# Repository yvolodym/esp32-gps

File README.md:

# esp32-gps

Akku-betriebenes GNSS-Empfänger-Board auf Basis des **ESP32**. Ein GNSS-Modul (GPS/BDS/GLONASS)
liefert die Positionsdaten, der ESP32 liest sie über UART aus und stellt sie per **Bluetooth**
für andere Geräte (z. B. Smartphone, Laptop, Navigationssoftware) bereit.

> Aktueller Stand: vollständiges KiCad-Hardwaredesign (Schaltplan + Platinenlayout). Die
> ESP32-Firmware (ESP-IDF) liest das GNSS-Modul per UART aus und gibt die NMEA-Sätze aktuell
> im Log aus; die Weiterleitung per Bluetooth folgt als nächster Schritt.

## Features

- **ESP32-PICO-V3** als zentrale MCU (WLAN + Bluetooth Classic/BLE integriert)
- **Ai-Thinker GP-01** GNSS-Modul (GPS/BDS/GLONASS) mit externer Antenne (Koax-Anschluss)
- **USB-C** für Programmierung (über integrierten CH340C USB-UART-Wandler) und zum Laden
- **Li-Ion-Akkubetrieb** (18650) mit Lade-IC TP4056, Akkuschutz (DW01A) und automatischer
  Umschaltung zwischen USB- und Akkuversorgung (LTC4412 Ideal-Diode-Power-Path)
- 3,3-V-Logikversorgung über AP2112K-3.3-LDO, ESD-Schutz am USB-Eingang

## Hardware

| Schaltplan | Inhalt |
|---|---|
| `kicad/esp32-gps.kicad_sch` | ESP32-PICO-V3, GNSS-Modul GP-01, USB-UART (CH340C), Antennenanschluss |
| `kicad/supply.kicad_sch` | Akku, Ladeschaltung, Power-Path, 3,3-V-Regler |
| `kicad/esp32-gps.kicad_pcb` | Platinenlayout |

Erstellt mit KiCad 9. Verwendete Zusatzbibliothek: [`yvolodym/kicad-libraries`](https://github.com/yvolodym).

## Firmware

ESP-IDF-Projekt (Framework-Version 6.0.2), Ziel-Chip `esp32`. Initialisiert UART2 auf den
Pins, die im Schaltplan als `GPS_TX`/`GPS_RX` verdrahtet sind (IO25/IO26), liest die NMEA-Sätze
des GP-01 zeilenweise ein und gibt sie per `ESP_LOGI` aus.

```
main/
  main.c          UART-Init + Log-Ausgabe der NMEA-Sätze
  CMakeLists.txt
CMakeLists.txt     Projekt-Root (ESP-IDF)
sdkconfig.defaults
```

Bauen/Flashen:

```sh
. $IDF_PATH/export.sh
idf.py set-target esp32
idf.py build
idf.py -p /dev/ttyUSB0 flash monitor
```

## Repo-Struktur

```
kicad/
  esp32-gps.kicad_pro   Projektdatei
  esp32-gps.kicad_sch   Hauptschaltplan
  supply.kicad_sch      Stromversorgung/Ladeschaltung
  esp32-gps.kicad_pcb   Platinenlayout
main/                   ESP-IDF-Firmware (GNSS-UART, aktuell Log-Ausgabe)
```

## Status / Roadmap

- [x] Schaltplan (MCU, GNSS, USB, Stromversorgung)
- [x] Platinenlayout
- [x] Firmware: GNSS-UART auslesen, NMEA-Sätze im Log ausgeben
- [ ] Bestückungsliste (BOM) / Fertigungsvorbereitung
- [ ] Firmware: NMEA-Daten per Bluetooth (SPP/BLE) bereitstellen
- [ ] Gehäuse

## Mitwirken

Projektsprache ist Deutsch – Commits, Issues und Doku bitte auf Deutsch verfassen.

Weitere Hinweise für die Arbeit mit Claude Code an diesem Projekt siehe [`CLAUDE.md`](./CLAUDE.md).

## Lizenz

Dieses Projekt steht unter der [CERN Open Hardware Licence Version 2 - Strongly Reciprocal
(CERN-OHL-S-2.0)](./LICENSE), einer verbreiteten Copyleft-Lizenz für offene Hardwareprojekte.

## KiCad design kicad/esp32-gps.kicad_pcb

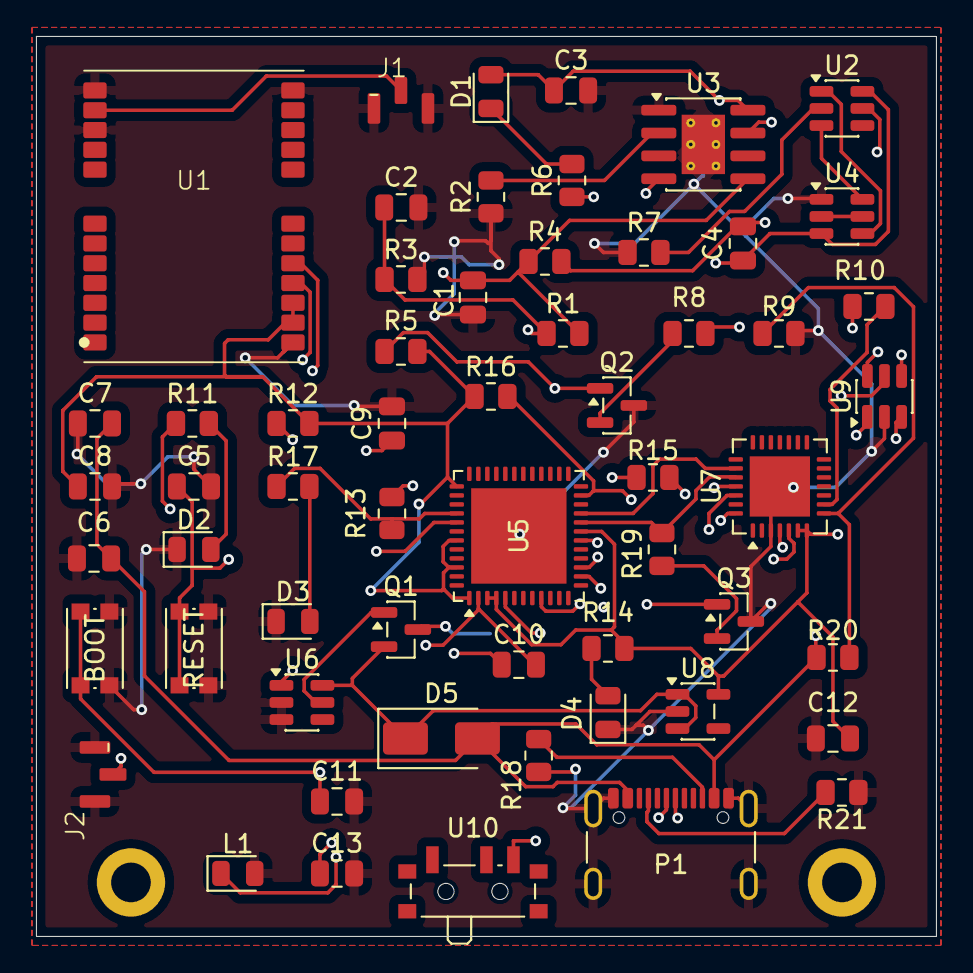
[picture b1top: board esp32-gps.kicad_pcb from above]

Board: 4 copper layers, 50.0 x 50.0 mm, 61 parts (1 on the bottom side), 45 nets.

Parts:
C1, C3, C6, C12: 10µF; C_0805_2012Metric
C2, C4, C5, C7, C11, C13: 100nF; C_0805_2012Metric
C8: 4,7µF; C_0805_2012Metric
C9: 2,7pF; C_0805_2012Metric
C10: 4,7pF; C_0805_2012Metric
D1: LED_RED; D_0805_2012Metric
D2: blue; D_0805_2012Metric
D3: green; D_0805_2012Metric
D4: LED_GREEN; D_0805_2012Metric
D5: SS14; D_SMA
H1, H2: MountingHole; MountingHole_2.2mm_M2_DIN965_Pad
J1, J2: MHF4
L1: 1,6nH; D_0805_2012Metric
P1: USB_C_Plug_USB2.0; USB_C_Receptacle_GCT_USB4105-xx-A_16P_TopMnt_Horizontal
Q1: Si2319CDS; SOT-23
Q2, Q3: BCW66G; SOT-23
R1: 220K; R_0805_2012Metric
R2: 2K; R_0805_2012Metric
R3: 100K; R_0805_2012Metric
R4: 100; R_0805_2012Metric
R5, R8, R12, R16, R19: 10K; R_0805_2012Metric
R6, R7, R10, R11, R17: 1K; R_0805_2012Metric
R9: 47.5K; R_0805_2012Metric
R13, R14, R15: 470; R_0805_2012Metric
R18, R21: 5.1k; R_0805_2012Metric
R20: 22.1K; R_0805_2012Metric
SW1: BOOT; SW_Push_1P1T_NO_CK_KMR2
SW2: RESET; SW_Push_1P1T_NO_CK_KMR2
U1: GP-01
U2: DW01A; SOT-23-6
U3: TP4056-42-ESOP8; SOIC-8-1EP_3.9x4.9mm_P1.27mm_EP2.41x3.3mm_ThermalVias
U4: U8205A; SOT-23-6
U5: ESP32-PICO-V3; QFN-48-1EP_7x7mm_P0.5mm_EP5.3x5.3mm
U6: LTC4412; TSOT-23-6
U7: CP2102N-Axx-xQFN28; QFN-28-1EP_5x5mm_P0.5mm_EP3.35x3.35mm
U8: AP2112K-3.3; SOT-23-5
U9: USBLC6-2P6; SOT-23-6
U10: Switch; SW_SPDT_PCM12
U11: Battery; CR2032

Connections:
+3.3V: C8.1, C12.1, C13.1, R5.1, R10.2, R12.2, R14.1, R16.1, U1.22 (VRTC), U1.23 (3V3), U5.1 (VDDA), U5.3 (VDDA3P3), U5.4 (VDDA3P3), U5.19 (VDD3P3_RTC), U5.37 (VDD3P3_CPU), U5.43 (VDDA), U5.46 (VDDA), U7.6 (VDD), U7.7 (VREGIN), U8.5 (VOUT)
+5V: C3.1, C6.1, C7.2, D1.2 (A), D5.2 (A), P1.A4 (VBUS), P1.A9 (VBUS), P1.B4 (VBUS), P1.B9 (VBUS), R20.2, U3.4 (V_{CC}), U3.8 (CE), U9.5 (VBUS)
/CTS: U5.21 (IO15), U7.23 (~CTS)
/DTR: R8.1, U7.28 (~DTR)
/EN: C5.1, Q2.1 (C), R5.2, SW2.2, U5.9 (EN)
/GPS_RX: U1.21 (RX0), U5.15 (IO26)
/GPS_TX: U1.20 (TX0), U5.14 (IO25)
/HVBAT: C1.1, Q1.3 (D), R1.2, R4.1, U3.5 (BAT), U6.1 (VIN), U11.1 (+)
/IO0: C11.1, Q3.1 (C), R16.2, SW1.1, U5.23 (IO0)
/RTS: R19.1, U5.20 (IO13), U7.24 (~RTS)
/RXD0: R13.2, R17.1, U5.40 (U0RXD/IO3)
/Supply/D+: U7.4 (D+), U9.6 (I/O1)
/Supply/D-: U7.5 (D-), U9.4 (I/O2)
/TXD0: R11.1, R15.2, U5.41 (U0TXD/IO1)
GND: C1.2, C2.2, C3.2, C5.2, C6.2, C7.1, C8.2, C9.2, C11.2, C12.2, C13.2, D2.1 (K), D3.1 (K), D4.1 (K), J1.2 (GND), J2.2 (GND), L1.2, P1.A1 (GND), P1.A12 (GND), P1.B1 (GND), P1.B12 (GND), P1.S1 (SHIELD), Q2.3 (E), Q3.3 (E), R2.1, R3.2, R7.1, R9.1, R18.2, R21.2, SW1.2, SW2.1, U1.10 (GND), U1.12 (GND), U1.13 (GND), U1.24 (GND), U3.1 (TEMP), U3.3 (GND), U3.9 (EPAD), U4.1 (S1), U5.49 (GND), U6.2 (GND), U6.3 (CTL), U7.3 (GND), U7.29 (GND), U8.2 (GND), U9.2 (GND)
unnamed: D3.2 (A), R17.2
unnamed: D2.2 (A), R11.2
unnamed: D1.1 (K), R6.2
unnamed: D5.1 (K), Q1.2 (S), U6.6 (SENSE), U8.1 (VIN), U8.3 (EN)
unnamed: D4.2 (A), R14.2
unnamed: C9.1, C10.1, J2.1 (SIGNAL)
unnamed: J1.1 (SIGNAL), U1.11 (RF)
unnamed: P1.A5 (CC), R21.1
unnamed: P1.A6 (D+), U9.1 (I/O1)
unnamed: P1.A7 (D-), U9.3 (I/O2)
unnamed: P1.B5 (VCONN), R18.1
unnamed: Q2.2 (B), R8.2
unnamed: Q3.2 (B), R19.2
unnamed: Q1.1 (G), U6.5 (GATE)
unnamed: R12.1, U5.18 (IO12)
unnamed: C10.2, L1.1, U5.2 (LNA_IN)
unnamed: C2.1, R1.1, R3.1, U5.5 (SENSOR_VP)
unnamed: R15.1, U7.25 (RXD)
unnamed: R13.1, U7.26 (TXD)
unnamed: R9.2, R20.1, U7.8 (VBUS)
unnamed: R10.1, U7.9 (~RST)
unnamed: R2.2, U3.2 (PROG)
unnamed: R6.1, U3.7 (~CHRG)
unnamed: U4.2 (D1), U4.5 (D2)
unnamed: U2.3 (OC), U4.6 (G1)
unnamed: U2.1 (OD), U4.4 (G2)
unnamed: C4.1, U2.6 (GND), U4.3 (S2), U10.3
unnamed: R7.2, U2.2 (CS)
unnamed: C4.2, R4.2, U2.5 (VCC)
unnamed: U10.2, U11.2 (-)
